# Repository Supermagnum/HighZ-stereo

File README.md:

A small PCB that uses a  OPA1679 op amp to amplify a signal from piezolectric crystals.

It has balanced output,input and should run on +48 phantom power.
Shielded cable must be used for connection to the piezo crystals.
Please use 0,5 W metal film resistors with 1% tolerance or better and audio quality capacitors.
Polypropylene (PP) capacitators is good, electrolytes if needed.

It is important that the circuit board is mounted inside a metal box, and Ø2mm conducting metal standoffs are used.
The corner pads of the PCB board is reserved for that.
Of course the PCB board and components must not come in contact with any metal surface expect the standoffs.

The circuit may benefit from a Zobel network, that is a 680 pF capacitor and a 150 ohms resistor in series between pin 2 and 3 on the output or the input connector. It should avoid high frequency oscillation in a long cable.

Schematic diagram: 
https://raw.githubusercontent.com/Supermagnum/HighZ-stereo/refs/heads/main/Highz-stereo.pdf

Component side:

https://github.com/Supermagnum/HighZ-stereo/blob/main/components-side.jpg

Reverse side:
https://github.com/Supermagnum/HighZ-stereo/blob/main/back-side.jpg

PCB board dimensions: 62.5X97.5 mm

BOM files:
https://github.com/Supermagnum/HighZ-stereo/tree/main/BOM-files

Piezoelectric disk, red wire for positive polarity.
Black for negative: https://github.com/Supermagnum/double-gain/blob/main/Piezo-element-6.jpg

They usually have a 3 pin XLR plug. Those are wired up like this: https://github.com/Supermagnum/piezo-balanced/blob/main/XLR%2BConnector%2BPinout%2BDiagram%2BRear%2BPin%2B2%2BHot%2Bv2%2Bgreen__01.jpg

NOTE:  
The XLR 3 pin plug has a solder lug for the shield for a reason.
It is my opinion that a shielded cable with 3 conductors inside is the best.
Suggested cable: Digi-Key Part Number:3242SL005-ND

Based on:
http://www.richardmudhar.com/blog/piezo-contact-microphone-hi-z-amplifier-low-noise-version/

Why: The problem with piezo guitar pickups and piezoelectric crystals is that they are not well matched to typical audio inputs. By their nature they can generate a lot of signal, but they cannot drive a 50 kilohm typical line input. The pickup needs to work into a much higher impedance, typically 1 megohm or so.

So what to people do? They go and plug a piezoelectric disks output directly into the line input of their recorder, typical impedance 50k, or the plug-in-power mic input of their recorder, typical impedance about 7k, and they start to bitch and moan that this damn thing sounds tinny. Which is does ! But they don't understand why!

The reason why these devices often sound tinny is because the piezo sensor presents its signal through a series capacitance which is small, typically 15nF or less. When wired to a normal 50 kilohm line input this forms a high-pass filter, which eliminates the bass.

This circuit board solves that, and amplifies the signal. How many dB it amplifies is dependent on the resistance on the resistors used.The data for that is on the schematic diagram.

It's fairly easy and straight forward to solder the components to the circuit board, a nice pointy soldering iron, solder, a magnifying glass, and a ohm or multimeter is all that is needed. Of course one needs a suitable metal box, and the circuit boards components must not come in contact with the metal box. That will cause short circuit, so it's best mounted on stand offs. Also, use the magnifying glass to check that no one of the soldering pads has been bridged.

It can be used for two reverb plates, listening to the insides of a engine,recording the sound of vibrating things. You will need 4 piezoelectric disks for that, mounted in two metal boxes Non electric conductive super glue is useable for that. Just glue them to a flat surface. The piezoelectric disks should be electrically insulated from the metal box.

Of course one can use a recorder like a tascam dr40x, as long as it can supply +48 volt phantom power, and has a headphone jack for monitoring.

A good set of headphones or ear protection with built in speakers will keep out unwanted sounds or noise.

Should also work nice with hydrophones. PZT-5H tubes is best for that. You want more gain, 35 or 40 dB for that. 
In case of dual hydrophones it's possible to have the hydrophones attached with two long cables. 

Some interesting ideas can be found in: https://github.com/Supermagnum/piezo-balanced/blob/main/Barlow-et-al-2008-HydrophoneConstruction_TM-417.pdf Note: Ecopoxy Flowcast does not need any vacuum, just a mold and a way to hold the piezoelectric tubes centered. It's also safer to work with.

Some methods of mounting a piezoelectric disk can be found here: https://locusonus.org/wiki/index.php?page=Hydrophone.en

Made with: http://www.kicad.org/

KiCad uses an integrated environment for all of the stages of the design process: Schematic capture, PCB layout, Gerber file generation/visualization, and library editing.

KiCad is a cross-platform program, and free!

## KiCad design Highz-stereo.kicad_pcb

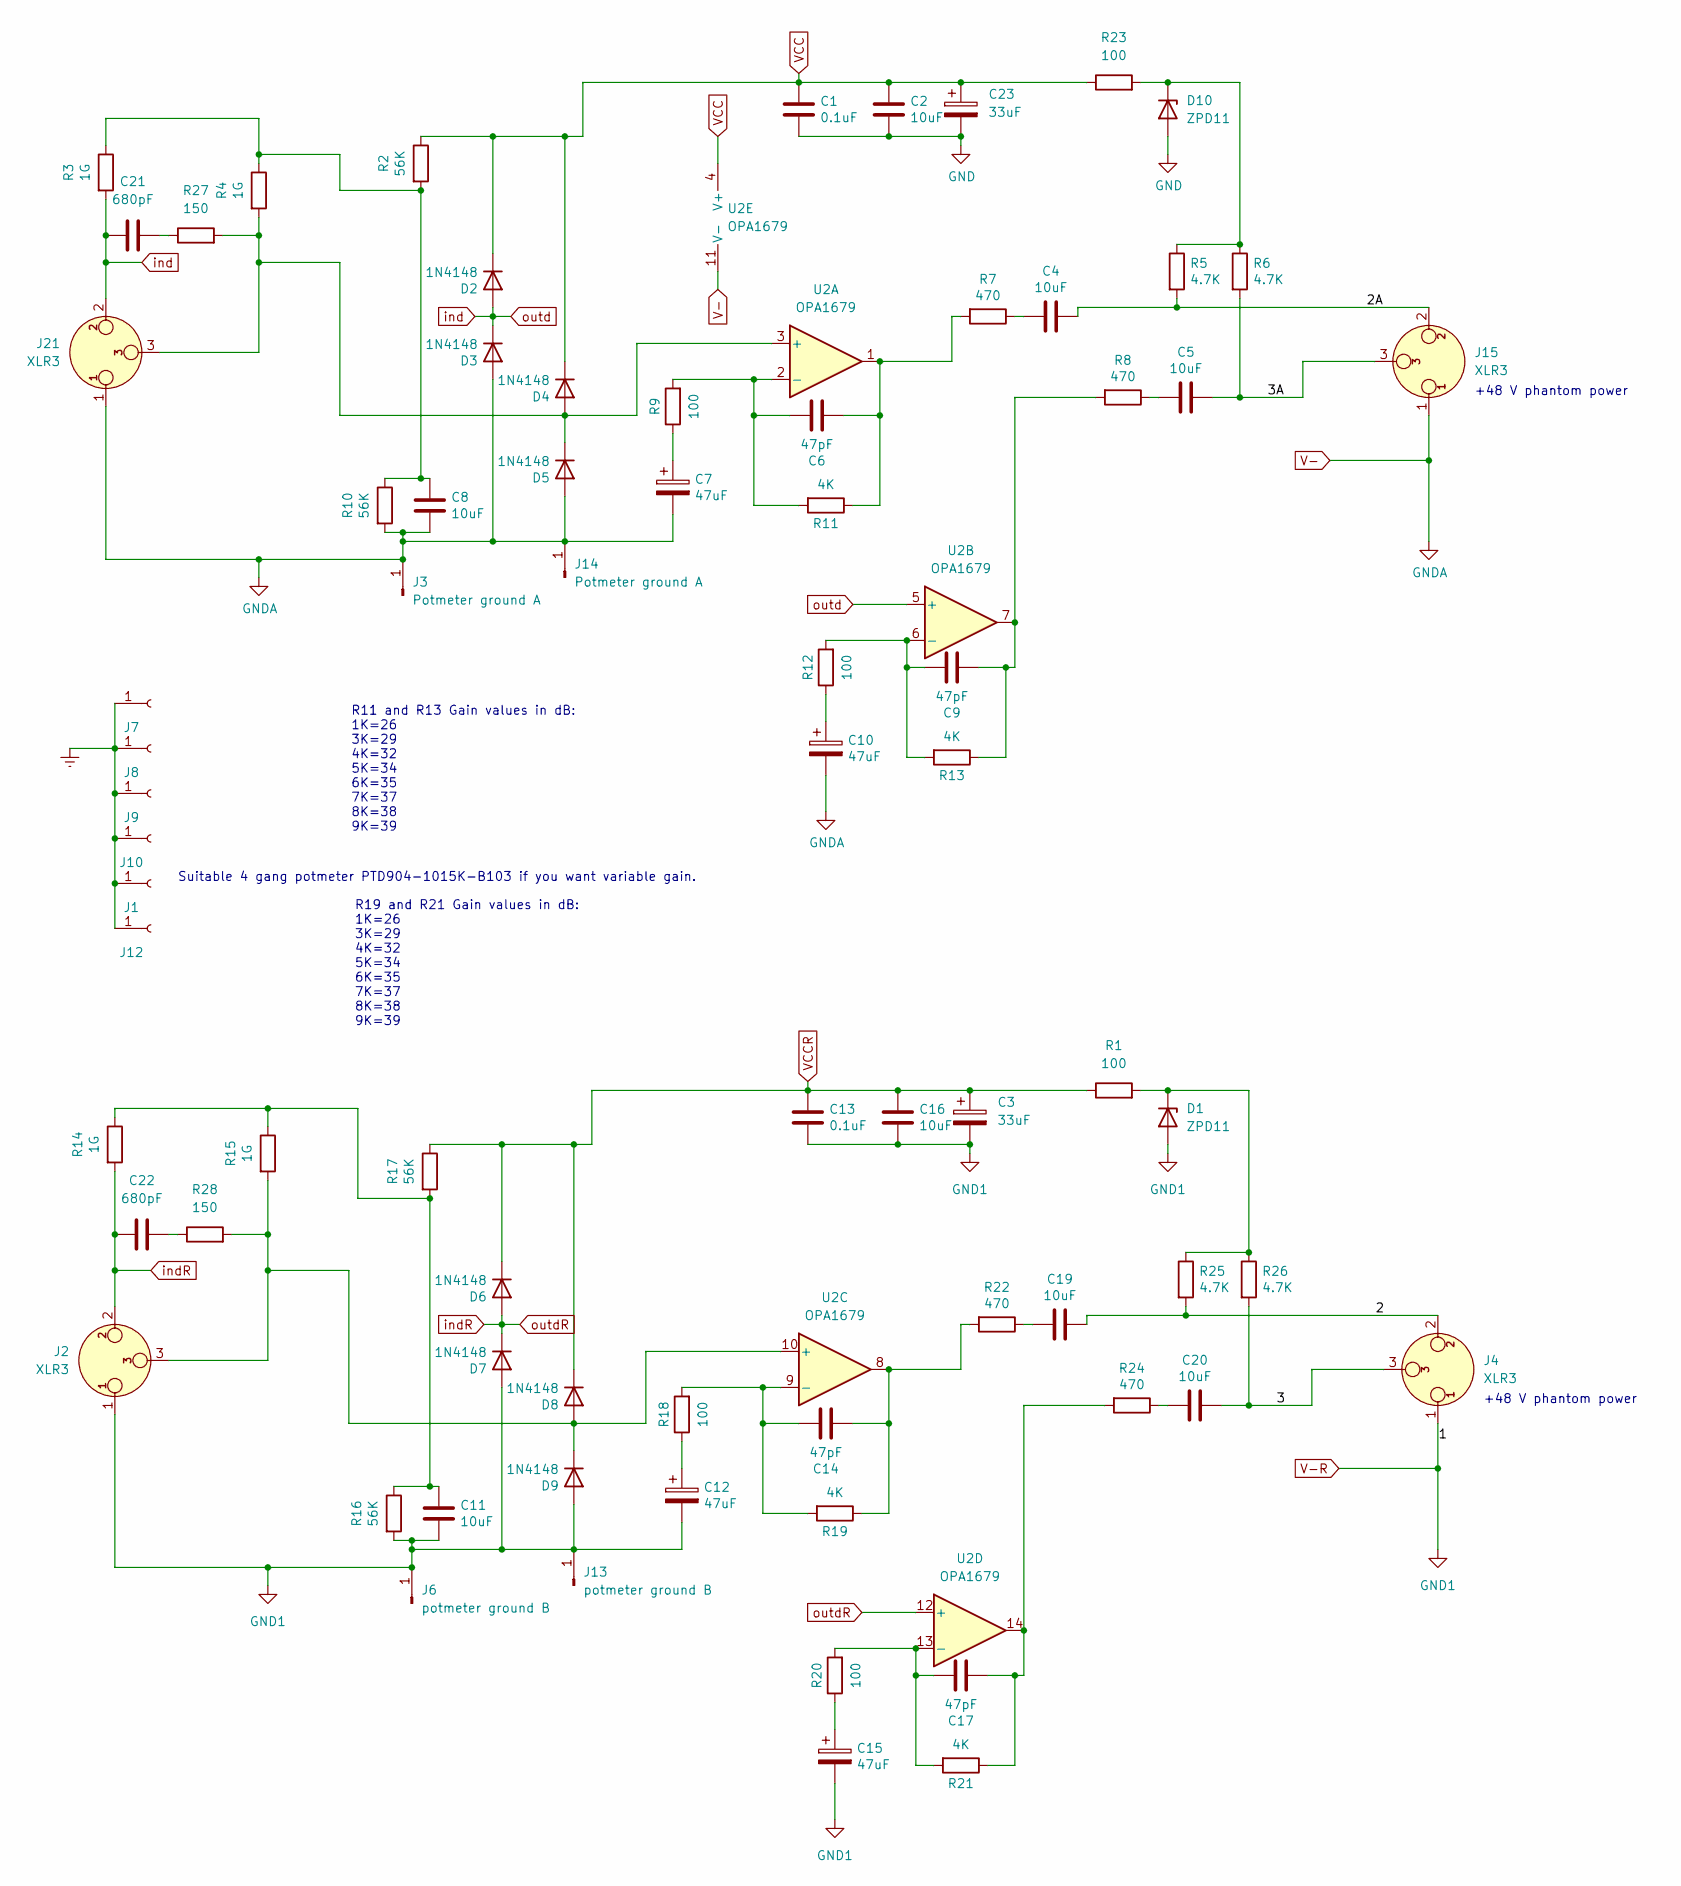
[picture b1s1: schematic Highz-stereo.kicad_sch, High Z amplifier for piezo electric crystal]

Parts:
C1, C13: 0.1uF; C_Disc_D5.0mm_W2.5mm_P2.50mm
C2, C4, C5, C8, C11, C16, C19, C20: 10uF; C_Rect_L18.0mm_W9.0mm_P15.00mm_FKS3_FKP3
C3, C23: 33uF; CP_Radial_D5.0mm_P2.00mm
C6, C9, C14, C17: 47pF; C_Rect_L7.2mm_W4.5mm_P5.00mm_FKS2_FKP2_MKS2_MKP2
C7, C10, C12, C15: 47uF; CP_Radial_D8.0mm_P3.50mm
C21, C22: 680pF; C_Rect_L7.0mm_W4.5mm_P5.00mm
D1, D10: ZPD11; D_DO-35_SOD27_P10.16mm_Horizontal
D2, D3, D4, D5, D6, D7, D8, D9: 1N4148; D_DO-35_SOD27_P7.62mm_Horizontal
J1, J7, J8, J9, J10, J12: Conn_01x01_Female; MountingHole_2.2mm_M2_ISO7380_Pad
J2, J4, J15, J21: XLR3; SolderWire-0.25sqmm_1x03_P4.5mm_D0.65mm_OD2mm
J3, J14: Potmeter ground A; PinHeader_1x01_P1.00mm_Vertical
J6, J13: potmeter ground B; PinHeader_1x01_P1.00mm_Vertical
R1, R9, R12, R18, R20, R23: 100; R_Axial_DIN0204_L3.6mm_D1.6mm_P5.08mm_Horizontal
R2, R10, R16, R17: 56K; R_Axial_DIN0204_L3.6mm_D1.6mm_P5.08mm_Horizontal
R3, R4, R14, R15: 1G; R_Axial_DIN0204_L3.6mm_D1.6mm_P5.08mm_Horizontal
R5, R6, R25, R26: 4.7K; R_Axial_DIN0204_L3.6mm_D1.6mm_P5.08mm_Horizontal
R7, R8, R22, R24: 470; R_Axial_DIN0204_L3.6mm_D1.6mm_P5.08mm_Horizontal
R11, R13, R19, R21: 4K; R_Axial_DIN0204_L3.6mm_D1.6mm_P5.08mm_Horizontal
R27, R28: 150; R_Axial_DIN0204_L3.6mm_D1.6mm_P5.08mm_Horizontal
U2: OPA1679; SOIC-14_3.9x8.7mm_P1.27mm

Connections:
/2: C19.1, J4.2, R25.2
/2A: C4.1, J15.2, R5.2
/3: C20.1, J4.3, R26.2
/3A: C5.1, J15.3, R6.2
Earth: J1.1, J7.1, J8.1, J9.1, J10.1, J12.1
GND: C1.2, C2.2, C23.2, D10.2 (A)
unnamed: C4.2, R7.1
unnamed: C5.2, R8.1
unnamed: C6.2, R7.2, R11.1, U2.1
unnamed: C7.1, R9.1
unnamed: C8.1, R2.2, R3.1, R4.1, R10.1
unnamed: C9.2, R8.2, R13.1, U2.7
unnamed: C10.1, R12.1
unnamed: C11.1, R14.1, R15.1, R16.1, R17.2
unnamed: C12.1, R18.1
unnamed: C14.2, R19.1, R22.2, U2.8
unnamed: C15.1, R20.1
unnamed: C17.2, R21.1, R24.2, U2.14
unnamed: C19.2, R22.1
unnamed: C20.2, R24.1
unnamed: C21.2, R27.1
unnamed: C22.2, R28.1
unnamed: D1.1 (K), R1.2, R25.1, R26.1
unnamed: D4.2 (A), D5.1 (K), J21.3, R4.2, R27.2, U2.3 (+)
unnamed: D8.2 (A), D9.1 (K), J2.3, R15.2, R28.2, U2.10 (+)
unnamed: D10.1 (K), R5.1, R6.1, R23.2
unnamed: C6.1, R9.2, R11.2, U2.2 (-)
unnamed: C9.1, R12.2, R13.2, U2.6 (-)
unnamed: C14.1, R18.2, R19.2, U2.9 (-)
unnamed: C17.1, R20.2, R21.2, U2.13 (-)
V-: C7.2, C8.2, C10.2, D3.2 (A), D5.2 (A), J3.1, J14.1, J15.1, J21.1, R10.2, U2.11 (V-)
V-R: C3.2, C11.2, C12.2, C13.2, C15.2, C16.2, D1.2 (A), D7.2 (A), D9.2 (A), J2.1, J4.1, J6.1, J13.1, R16.2
VCC: C1.1, C2.1, C23.1, D2.1 (K), D4.1 (K), R2.1, R23.1, U2.4 (V+)
VCCR: C3.1, C13.1, C16.1, D6.1 (K), D8.1 (K), R1.1, R17.1
ind: C21.1, D2.2 (A), D3.1 (K), J21.2, R3.2, U2.5 (+)
indR: C22.1, D6.2 (A), D7.1 (K), J2.2, R14.2, U2.12 (+)

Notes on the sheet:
Suitable 4 gang potmeter PTD904-1015K-B103 if you want variable gain.
+48 V phantom power
R19 and R21 Gain values in dB: 1K=26 3K=29 4K=32 5K=34 6K=35 7K=37 8K=38 9K=39
R11 and R13 Gain values in dB: 1K=26 3K=29 4K=32 5K=34 6K=35 7K=37 8K=38 9K=39

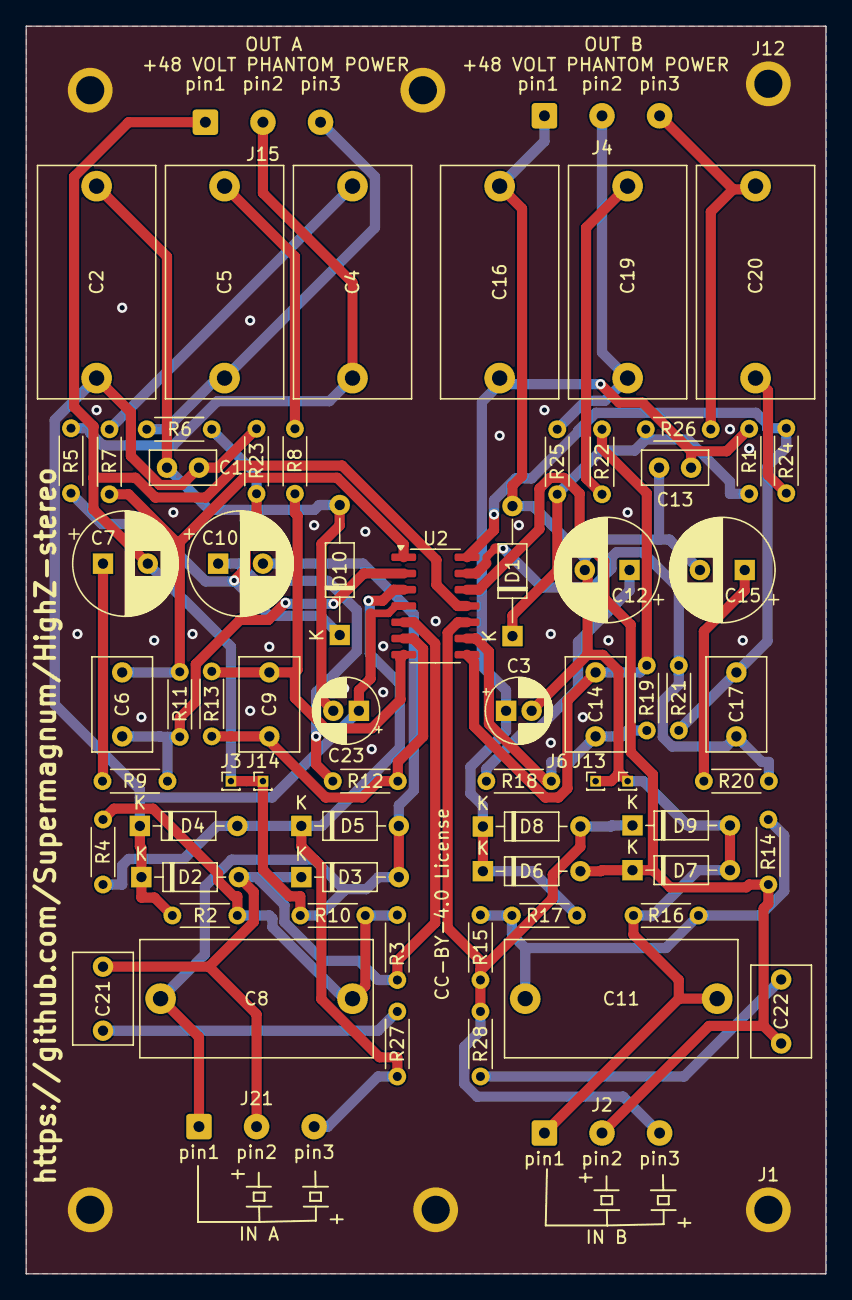
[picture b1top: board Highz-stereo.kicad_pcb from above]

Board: 2 copper layers, 62.5 x 97.5 mm, 75 parts (0 on the bottom side), 36 nets.

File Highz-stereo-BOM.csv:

"Reference","Value","Datasheet","Footprint","Qty","DNP","mfr"
"C1,C13","0.1uF","~","Capacitor_THT:C_Disc_D5.0mm_W2.5mm_P2.50mm","2","","  TAP104K050SCS"
"C2,C4,C5,C8,C11,C16,C19,C20","10uF","~","Capacitor_THT:C_Rect_L18.0mm_W9.0mm_P15.00mm_FKS3_FKP3","8","","  B32522C0106K000"
"C3,C23","33uF","~","Capacitor_THT:CP_Radial_D5.0mm_P2.00mm","2","","  860010672011"
"C6,C9,C14,C17","47pF","~","Capacitor_THT:C_Rect_L7.2mm_W4.5mm_P5.00mm_FKS2_FKP2_MKS2_MKP2","4","","  FKP2O100471D00KSSD"
"C7,C10,C12,C15","47uF","~","Capacitor_THT:CP_Radial_D8.0mm_P3.50mm","4","","  ECA-2AM470BJ"
"C21,C22","680pF","~","Capacitor_THT:C_Rect_L7.0mm_W4.5mm_P5.00mm","2","","  FKP2D006801D00KSSD"
"D1,D10","ZPD11","http://diotec.com/tl_files/diotec/files/pdf/datasheets/zpd1","Diode_THT:D_DO-35_SOD27_P10.16mm_Horizontal","2","","  ZPD11"
"D2,D3,D4,D5,D6,D7,D8,D9","1N4148","~","Diode_THT:D_DO-35_SOD27_P7.62mm_Horizontal","8","","  1N4148"
"J1,J7,J8,J9,J10,J12","Conn_01x01_Female","~","MountingHole:MountingHole_2.2mm_M2_ISO7380_Pad","6","",""
"J2,J4,J15,J21","XLR3","~","Connector_Wire:SolderWire-0.25sqmm_1x03_P4.5mm_D0.65mm_OD2mm","4","",""
"J3,J14","Potmeter ground A","~","Connector_PinHeader_1.00mm:PinHeader_1x01_P1.00mm_Vertical","2","",""
"J6,J13","potmeter ground B","~","Connector_PinHeader_1.00mm:PinHeader_1x01_P1.00mm_Vertical","2","",""
"R1,R9,R12,R18,R20,R23","100","~","Resistor_THT:R_Axial_DIN0204_L3.6mm_D1.6mm_P5.08mm_Horizontal","6","","  YR1B100RCC"
"R2,R10,R16,R17","56K","~","Resistor_THT:R_Axial_DIN0204_L3.6mm_D1.6mm_P5.08mm_Horizontal","4","","  RNMF14FTC56K0"
"R3,R4,R14,R15","1G","~","Resistor_THT:R_Axial_DIN0204_L3.6mm_D1.6mm_P5.08mm_Horizontal","4","","  RGP0207CHK1G0"
"R5,R6,R25,R26","4.7K","~","Resistor_THT:R_Axial_DIN0204_L3.6mm_D1.6mm_P5.08mm_Horizontal","4","","  RNMF14FTC4K70"
"R7,R8,R22,R24","470","~","Resistor_THT:R_Axial_DIN0204_L3.6mm_D1.6mm_P5.08mm_Horizontal","4","","  MFR-25FTE52-470R"
"R11,R13,R19,R21","4K","~","Resistor_THT:R_Axial_DIN0204_L3.6mm_D1.6mm_P5.08mm_Horizontal","4","","  RN60D4001FRE6"
"R27,R28","150","~","Resistor_THT:R_Axial_DIN0204_L3.6mm_D1.6mm_P5.08mm_Horizontal","2","","  RNF14FTD150R"
"U2","OPA1679","http://www.ti.com/lit/ds/symlink/opa1678.pdf","Package_SO:SOIC-14_3.9x8.7mm_P1.27mm","1","","OPA1679IDR"

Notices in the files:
Highz-stereo.kicad_pcb:
CC-BY-4.0 License
